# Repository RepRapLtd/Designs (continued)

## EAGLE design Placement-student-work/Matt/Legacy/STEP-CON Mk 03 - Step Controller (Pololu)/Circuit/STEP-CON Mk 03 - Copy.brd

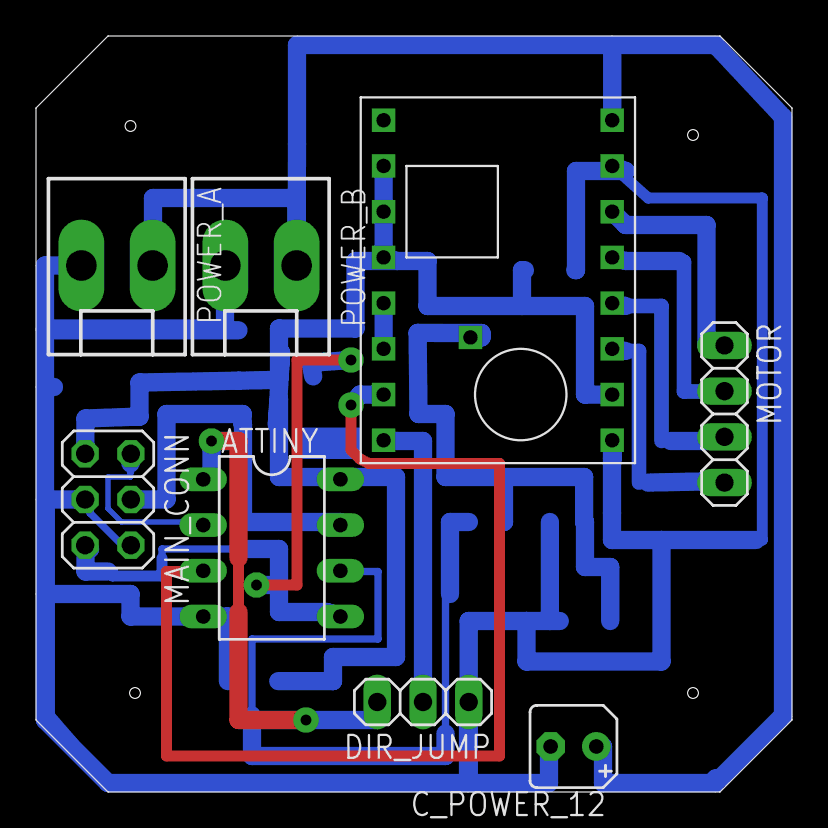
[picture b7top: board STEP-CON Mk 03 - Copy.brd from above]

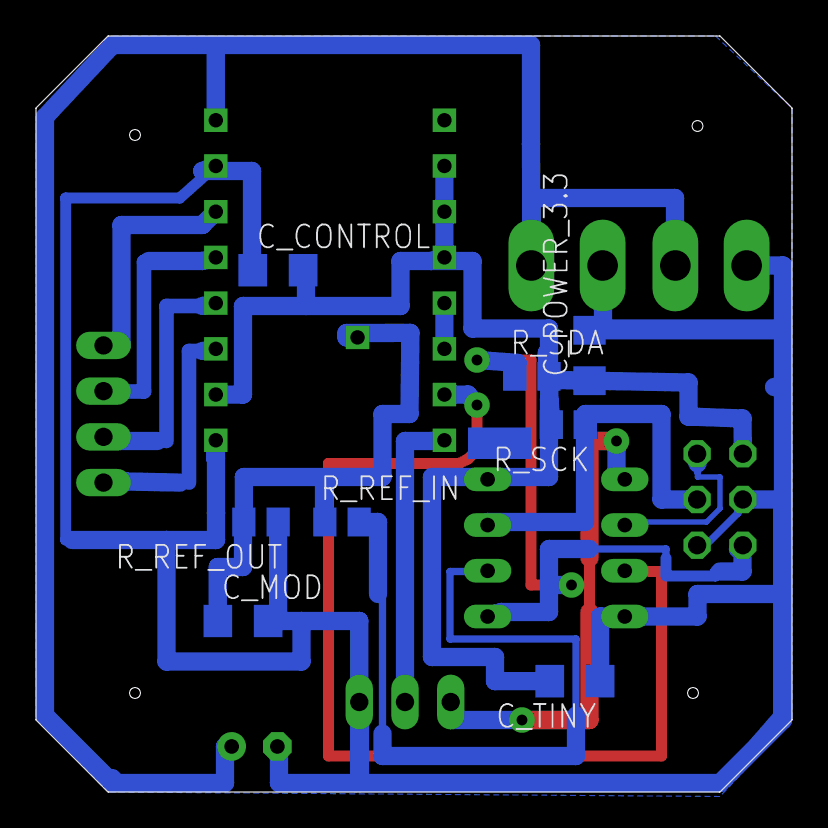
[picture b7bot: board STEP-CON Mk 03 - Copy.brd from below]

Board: 2 copper layers, 42.0 x 42.0 mm, 16 parts (8 on the bottom side), 16 nets.

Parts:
ATTINY: DIL08
C_CONTROL: 0.1u; C1206
C_MOD: 0.1u; C1206
C_POWER_3.3: 10u; C1206
C_POWER_12: 100uF; B45181A
C_TINY: 0.1u; C1206
DIR_JUMP: 1X03
MAIN_CONN: 2X03
MOTOR: 1X04
POWER_A: KK-156-2
POWER_B: KK-156-2
R_REF_IN: 47K; M0805
R_REF_OUT: 7K; M0805
R_SCK: 4K7; M0805
R_SDA: 4K7; M0805
U$1: MD09B_MOD; MD90B_MOD

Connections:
1A: MOTOR.3, U$1.1A
1B: MOTOR.4, U$1.1B
2A: MOTOR.2, U$1.2A
2B: MOTOR.1, U$1.2B
+3V3: ATTINY.8, C_CONTROL.2, C_POWER_3.3.1, C_TINY.2, MAIN_CONN.1, R_SCK.2, R_SDA.2, U$1.MS1, U$1.MS2, U$1.MS3, U$1.VDD
+12V: C_POWER_12.+, POWER_A.1, POWER_B.1, U$1.VMOT
DIR: DIR_JUMP.2, U$1.DIR
GND: ATTINY.4, C_CONTROL.1, C_MOD.2, C_POWER_3.3.2, C_POWER_12.-, C_TINY.1, DIR_JUMP.1, MAIN_CONN.3, MAIN_CONN.6, POWER_A.2, POWER_B.2, R_REF_OUT.1, U$1.GND, U$1.GND(2)
PWM: ATTINY.6, R_REF_IN.2
REF: C_MOD.1, R_REF_IN.1, R_REF_OUT.2, U$1.REF
RESET/DIR: ATTINY.1, DIR_JUMP.3
RST_SLP: U$1.RST, U$1.SLP
SCK: ATTINY.7, MAIN_CONN.4, R_SCK.1
SDA: ATTINY.5, MAIN_CONN.5, R_SDA.1
SKYCLOCK: ATTINY.2, MAIN_CONN.2
STEP: ATTINY.3, U$1.STEP
